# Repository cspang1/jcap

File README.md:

<h1 align="center"></h1>

<p align="center"><b>Check out the <a href="https://github.com/cspang1/JCAP/wiki">Project Wiki</a> for the development log</b></p> 
<p align="center"><b>A custom game resource creation software suite <a href="https://github.com/cspang1/jide">is being developed</a> for the inaugural JCAP release!</b></p> 

<hr>

<p>JCAP is a project with the goal of developing a <a href="https://www.mikesarcade.com/cgi-bin/spies.cgi?action=url&type=pinout&page=Jamma.html">JAMMA arcade standard</a> compatible game board using the <a href="https://www.parallax.com/product/p8x32a-q44">Parallax Propeller 1 (P8X32A) microcontroller</a> upon which a user can implement their own custom arcade game, either from scratch or by using the library of graphics, sound, input, and other drivers developed under the project. Ultimately, the project will provide all of the following in such a way that a user has everything they need to implement their own arcade game and have a PCB printed to build it on:</p>

<ul>
  <li>VGA video driver</li>
  <li>Sprite/tile based graphics driver</li>
  <li>PWM sound driver</li>
  <li>Serialized input driver</li>
  <li>Game engine</li>
  <li>Board schematic</li>
  <li>PCB .gerber files</li>
  <li>PCB BOM</li>
</ul>

<h1 align="center">Contribution Guidelines</h1>
<p>On the off chance anyone is interested in contributing to JCAP, there are some basic standards which should be ahered to:</p>

<ol>
  <li>Document everything! For code documentation, use existing code (e.g. Dev/Input/Software/input.spin) as an example. PASM should be documented somewhat anal-retentively, line-by-line, with block comments for routines and subroutines. Header comments should follow the same standard established by existing code as well.</li>
  <li>Any discovered problems/concerns/features that you won't be addressing with your current commit need to have an issue created and assigned to the appropriate person(s), tag, milestone, and project. This eliminates the risk of development amnesia. Additionally, when a commit has satisfied an issue, the commit hash should be referenced in the closing comment of the issue.</li>
  <li>Commit messages need to at a minimum broadly describe each change made to the repository. Whether it's fixing a bug, adding a feature, adding a new datasheet, or updating some indentation, one should be able to read the commit message and understand immediately what's been done to the repo.</li>
  <li>Any documents (manuals, datasheets, tutorials) which are critical to your contributions should be placed in their appropriate subdirectories in /Docs. For similarly important generic links, place them in "Useful Links.txt" in /Docs.</li>
</ol>

<p>Pull requests that don't follow these guidelines will be rejected until corrections have been made. While this all may seem like an over-processed waste of time, an auxiliary goal for JCAP is to create a project which maintains the highest possible standards to prevent headache down the road and belay confusion to anyone on the outside looking in.</p>

<h1 align="center">Current Contributors</h1>
<p>The following individuals have contributed to JCAP:</p>

<ul>
  <li>Connor Spangler (cspang1)</li>
  <li>Marko Lukat (konimaru)</li>
</ul>

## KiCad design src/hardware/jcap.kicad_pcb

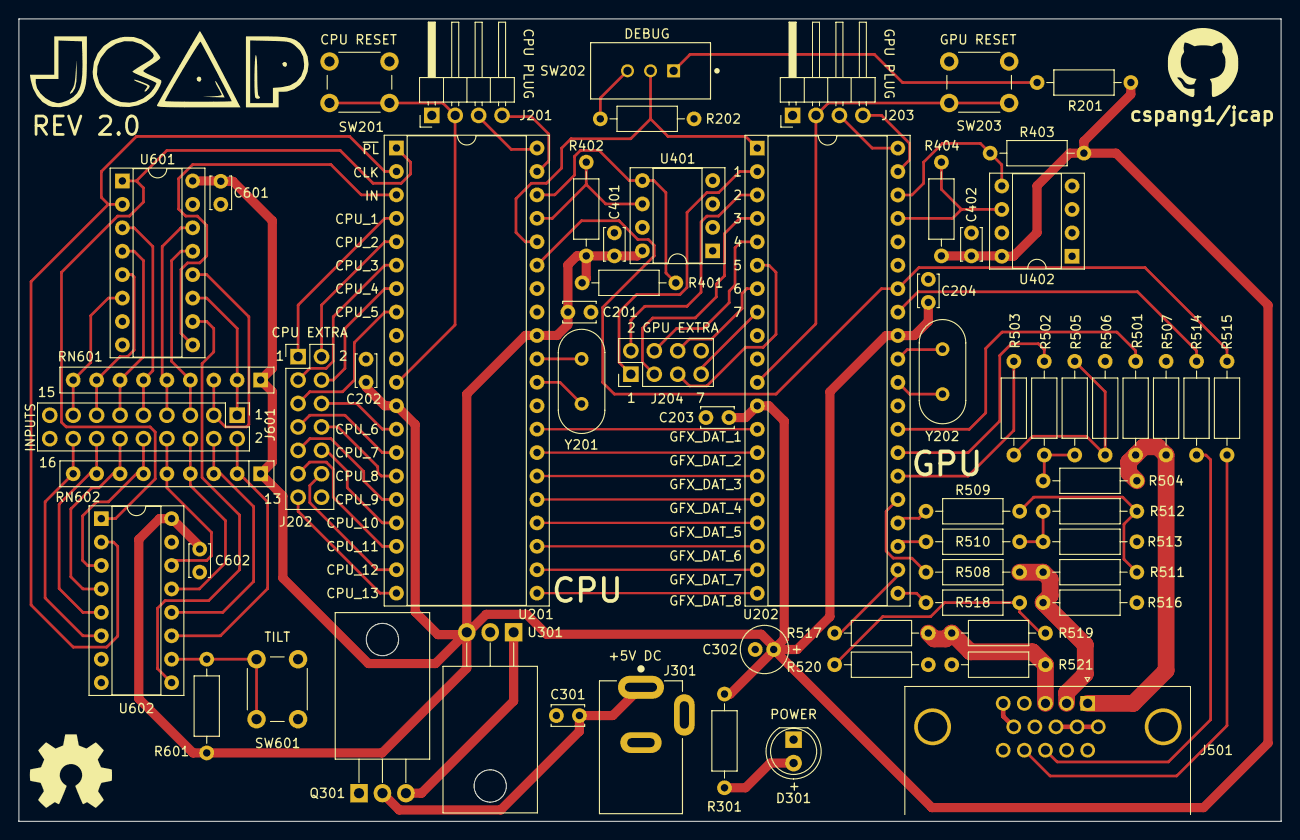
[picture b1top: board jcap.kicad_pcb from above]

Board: 2 copper layers, 136.8 x 87.0 mm, 63 parts (0 on the bottom side), 91 nets.

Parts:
C201, C202, C203, C204, C401, C402, C601, C602: 0.1u; C_Disc_D3.4mm_W2.1mm_P2.50mm
C301: .47u; C_Disc_D3.4mm_W2.1mm_P2.50mm
C302: 47u; C_Radial_D5.0mm_H11.0mm_P2.00mm
D301: POWER LED; LED_D5.0mm
J201: CPU PGMR; PinHeader_1x04_P2.54mm_Horizontal
J202: SPARE CPU HDR; PinHeader_2x07_P2.54mm_Vertical
J203: GPU PGMR; PinHeader_1x04_P2.54mm_Horizontal
J204: SPARE GPU HDR; PinHeader_2x04_P2.54mm_Vertical
J301: DC IN; CUI_PJ-202AH
J501: VGA OUT; 2311763-2
J601: CONTROLS; PinHeader_2x09_P2.54mm_Vertical
Q301: IPP80P03P4L-04; TO-220-3_Horizontal_TabDown
R201, R202, R601: 10K; R_Axial_DIN0207_L6.3mm_D2.5mm_P10.16mm_Horizontal
R301: 100; R_Axial_DIN0207_L6.3mm_D2.5mm_P10.16mm_Horizontal
R401, R402, R403, R404: 4.7K; R_Axial_DIN0207_L6.3mm_D2.5mm_P10.16mm_Horizontal
R501, R502, R503, R506, R508, R509, R510, R513: 309; R_Axial_DIN0207_L6.3mm_D2.5mm_P10.16mm_Horizontal
R504, R505, R511, R512: 154; R_Axial_DIN0207_L6.3mm_D2.5mm_P10.16mm_Horizontal
R507, R516: 147; R_Axial_DIN0207_L6.3mm_D2.5mm_P10.16mm_Horizontal
R514, R515: 220; R_Axial_DIN0207_L6.3mm_D2.5mm_P10.16mm_Horizontal
R517, R518, R520: 267; R_Axial_DIN0207_L6.3mm_D2.5mm_P10.16mm_Horizontal
R519: 133; R_Axial_DIN0207_L6.3mm_D2.5mm_P10.16mm_Horizontal
R521: 174; R_Axial_DIN0207_L6.3mm_D2.5mm_P10.16mm_Horizontal
RN601, RN602: 10K; R_Array_SIP9
SW201: CPU ~{RES}; SW_PUSH_6mm_H5mm
SW202: DEBUG; SW_1825159-1
SW203: GPU ~{RES}; SW_PUSH_6mm_H5mm
SW601: TILT; SW_PUSH_6mm_H5mm
U201, U202: P8X32A; DIP-40_W15.24mm_Socket
U301: LM3940IT; TO-220-3_Horizontal_TabDown
U401, U402: 24LC256; DIP-8_W7.62mm_Socket
U601, U602: 74HC165; DIP-16_W7.62mm_Socket
Y201, Y202: 6.5MHz; Crystal_HC49-U_Vertical

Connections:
+3.3V: C201.2, C202.2, C203.2, C204.2, C302.1, C401.2, C402.2, C601.2, C602.2, R201.2, R301.1, R401.2, R402.2, R403.2, R404.2, R601.2, RN601.1 (common), RN602.1 (common), U201.12 (VDD), U201.32 (VDD), U202.12 (VDD), U202.32 (VDD), U301.3 (OUT), U401.8 (VCC), U402.8 (VCC), U601.16 (VCC), U602.16 (VCC)
/Input/IN1: J601.1, RN601.2 (R1), U601.11 (D0)
/Input/IN2: J601.3, RN601.3 (R2), U601.12 (D1)
/Input/IN3: J601.5, RN601.4 (R3), U601.13 (D2)
/Input/IN4: J601.7, RN601.5 (R4), U601.14 (D3)
/Input/IN5: J601.9, RN601.6 (R5), U601.3 (D4)
/Input/IN6: J601.11, RN601.7 (R6), U601.4 (D5)
/Input/IN7: J601.13, RN601.8 (R7), U601.5 (D6)
/Input/IN8: J601.15, RN601.9 (R8), U601.6 (D7)
/Input/IN9: J601.2, RN602.2 (R1), U602.11 (D0)
/Input/IN10: J601.4, RN602.3 (R2), U602.12 (D1)
/Input/IN11: J601.6, RN602.4 (R3), U602.13 (D2)
/Input/IN12: J601.8, RN602.5 (R4), U602.14 (D3)
/Input/IN13: J601.10, RN602.6 (R5), U602.3 (D4)
/Input/IN14: J601.12, RN602.7 (R6), U602.4 (D5)
/Input/IN15: J601.14, RN602.8 (R7), U602.5 (D6)
/Input/IN16: J601.16, RN602.9 (R8), U602.6 (D7)
/Input/SHIFT_IN: U601.10 (DS), U602.9 (Q7)
/Propellers/CPU_SPARE_1: J202.1, U201.4 (P3)
/Propellers/CPU_SPARE_2: J202.2, U201.5 (P4)
/Propellers/CPU_SPARE_3: J202.3, U201.6 (P5)
/Propellers/CPU_SPARE_4: J202.4, U201.7 (P6)
/Propellers/CPU_SPARE_5: J202.5, U201.8 (P7)
/Propellers/CPU_SPARE_6: J202.6, U201.13 (P8)
/Propellers/CPU_SPARE_7: J202.7, U201.14 (P9)
/Propellers/CPU_SPARE_8: J202.8, U201.15 (P10)
/Propellers/CPU_SPARE_9: J202.9, U201.16 (P11)
/Propellers/CPU_SPARE_10: J202.10, U201.17 (P12)
/Propellers/CPU_SPARE_11: J202.11, U201.18 (P13)
/Propellers/CPU_SPARE_12: J202.12, U201.19 (P14)
/Propellers/CPU_SPARE_13: J202.13, U201.20 (P15)
/Propellers/DEBUG: SW202.2, U201.36 (P27), U202.1 (P0)
/Propellers/GFX_DAT_1: U201.28 (P23), U202.13 (P8)
/Propellers/GFX_DAT_2: U201.27 (P22), U202.14 (P9)
/Propellers/GFX_DAT_3: U201.26 (P21), U202.15 (P10)
/Propellers/GFX_DAT_4: U201.25 (P20), U202.16 (P11)
/Propellers/GFX_DAT_5: U201.24 (P19), U202.17 (P12)
/Propellers/GFX_DAT_6: U201.23 (P18), U202.18 (P13)
/Propellers/GFX_DAT_7: U201.22 (P17), U202.19 (P14)
/Propellers/GFX_DAT_8: U201.21 (P16), U202.20 (P15)
/Propellers/GPU_SPARE_1: J204.1, U202.2 (P1)
/Propellers/GPU_SPARE_2: J204.2, U202.3 (P2)
/Propellers/GPU_SPARE_3: J204.3, U202.4 (P3)
/Propellers/GPU_SPARE_4: J204.4, U202.5 (P4)
/Propellers/GPU_SPARE_5: J204.5, U202.6 (P5)
/Propellers/GPU_SPARE_6: J204.6, U202.7 (P6)
/Propellers/GPU_SPARE_7: J204.7, U202.8 (P7)
/Propellers/SER_RX_CPU: J201.4, U201.39 (P30)
/Propellers/SER_RX_GPU: J203.4, U202.39 (P30)
/Propellers/SER_TX_CPU: J201.3, U201.40 (P31)
/Propellers/SER_TX_GPU: J203.3, U202.40 (P31)
/Propellers/~SER_RES_CPU: J201.2, SW201.2, U201.11 (~RES)
/Propellers/~SER_RES_GPU: J203.2, SW203.2, U202.11 (~RES)
/VGA_DAC/BLUE_OUT: J501.3, R517.1, R519.1, R521.2
/VGA_DAC/GREEN_OUT: J501.2, R508.1, R511.1, R516.2
/VGA_DAC/RED_OUT: J501.1, R501.1, R504.1, R507.2
BLUE1: R517.2, U202.22 (P17)
BLUE2: R518.2, U202.21 (P16)
GND: C201.1, C202.1, C203.1, C204.1, C301.1, C302.2, C401.1, C402.1, C601.1, C602.1, D301.1 (K), J201.1, J202.14, J203.1, J204.8, J301.2, J301.3, J501.0, J501.5, J501.6, J501.7, J501.8, J501.10, J601.17, J601.18, Q301.1 (G), R202.2, R506.2, R507.1, R513.2, R516.1, R520.2, R521.1, SW201.1, SW203.1, SW601.1, U201.9 (VSS), U201.10 (~BOE), U201.29 (VSS), U202.9 (VSS), U202.10 (~BOE), U202.29 (VSS), U301.2 (GND), U401.1 (A0), U401.2 (A1), U401.3 (A2), U401.4 (GND), U401.7 (WP), U402.1 (A0), U402.2 (A1), U402.3 (A2), U402.4 (GND), U402.7 (WP), U601.8 (GND), U601.15 (~CE), U602.8 (GND), U602.15 (~CE)
GREEN1: R508.2, U202.25 (P20)
GREEN2: R509.2, U202.24 (P19)
GREEN3: R510.2, U202.23 (P18)
H_SYNC: R514.1, U202.33 (P24)
INPUTS: U201.3 (P2), U601.9 (Q7)
INPUTS_CLK: U201.2 (P1), U601.2 (CP), U602.2 (CP)
unnamed: D301.2 (A), R301.2
unnamed: J501.13, R514.2
unnamed: J501.14, R515.2
unnamed: C301.2, J301.1, Q301.2 (D)
unnamed: Q301.3 (S), U301.1 (IN)
unnamed: R201.1, SW202.1
unnamed: R202.1, SW202.3
unnamed: R502.1, R504.2, R505.1
unnamed: R503.1, R505.2, R506.1
unnamed: R509.1, R511.2, R512.1
unnamed: R510.1, R512.2, R513.1
unnamed: R518.1, R519.2, R520.1
unnamed: U201.30 (XI), Y201.2
unnamed: U201.31 (XO), Y201.1
unnamed: U202.30 (XI), Y202.2
unnamed: U202.31 (XO), Y202.1
unnamed: R601.1, SW601.2, U602.10 (DS)
RED1: R501.2, U202.28 (P23)
RED2: R502.2, U202.27 (P22)
RED3: R503.2, U202.26 (P21)
SCL_CPU: R402.1, U201.37 (P28), U401.6 (SCL)
SCL_GPU: R404.1, U202.37 (P28), U402.6 (SCL)
SDA_CPU: R401.1, U201.38 (P29), U401.5 (SDA)
SDA_GPU: R403.1, U202.38 (P29), U402.5 (SDA)
V_SYNC: R515.1, U201.35 (P26), U202.34 (P25)
~INPUTS_PL: U201.1 (P0), U601.1 (~PL), U602.1 (~PL)

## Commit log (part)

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2017-06-06 Minor cosmetic change to input.spin
2017-06-06 Refactored input.spin layout
2017-06-06 Fixed README.md formatting
2017-06-07 Added links concerning 240p video to Useful Links.txt
2017-06-10 Created wip/video/vga branch for developing VGA video. Added a couple DAC examples. Created vga.spin file.
2017-06-14 Updated counter PLL calculator
2017-06-15 Began adding video generation logic to vga.spin. Populated counter PLL calculator w/ 640x480 @ 60 Hz values.
2017-10-26 Started adding test code/values to develop a monochromatic 640x480 60Hz VGA routine
2017-10-27 Modified vga.spin to implement vertical sync area; full vga monochromatic measuring via oscilloscope ready
2017-10-27 Updated, moved, and renamed P8X32A/DE0-Nano pinout image
2017-10-27 Modified vga.spin so test colors step up gradually for testing. Added R-2R_DAC.asc LTSpice circuit model to test and verify VGA DAC functionality.
2017-10-27 .gitignore is now working
2017-10-28 Updated vga.spin commenting
2017-10-30 Updated vga.spin VGA driver to render @ 16x16 pixel tile demensions of 10x12 tiles to support tile graphics also added for next iteration of testing
2017-10-30 Began implementing tile-based graphics
2017-10-30 Updated vga.spin to correctly reference tile pointers (par passed to cog only contains address of address of tile/color resources, so needed extra rdlong)
2017-10-31 Updated vga.spin commenting. Added another tile map for testing. Removed fit directive.
2017-11-01 Objectified vga driver
2017-11-02 Refactored vga driver to be parameterized
2017-11-03 Added 8x8 compatible tile map to vga_test.spin, and reorganized tile palette to take into account video generator mirroring
2017-11-03 Update VGA driver comments
2017-11-04 Added link to wiki to readme
2017-11-04 Updated game logic to use inputs to manipulate and store x/y game position within game map boundary
2017-11-05 Prepared game.spin to perform scrolling via VGA driver
2017-11-05 Started refactoring game system to use rising edge input logic; running into apparent debouncing issue
2017-11-06 Updated vga.spin to change VGA outputs to highest 8 GPIO pins (freeing up LED outputs for testing). Updated game logic to update position registers via buttons as well as explicitly manipulate the ti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
2017-11-07 Updated compatible tile dimension calculator
2017-11-07 Refactored VGA driver to iteratively load hub variables into cog registers
2017-11-10 Prepared wip branches for multi-cog video dev
2017-11-10 Established multi-cog start/stop routines for graphics driver
2017-11-11 Added graphics stop routine and refactored
2017-11-13 Fixed misidentified bug w/ VGA driver start/stop via inputs
2017-11-14 Added VGA driver cog synchronization, and overhauled some commenting and implementation details
2017-11-15 Refactor in preparation for multicog overhaul
2017-11-16 Began multicog VGA refactor; currently experiencing bizarre behavior w/ only > 2 cogs working.
2017-11-17 Continued refactor of graphics/VGA system
2017-11-19 Began integrating tile map system with multicog VGA driver
2017-11-20 Minor multicog refactor modifications
2017-11-21 Removed unecessary variable reservations
2017-11-22 Corrected errant buffer reading/writing
2017-11-22 Minor multicog VGA driver logic refactor
2017-11-22 Refactored VGA tile and color retrieval
2017-11-23 Heavily refactored VGA/graphics system to reduce memory footprint
2018-01-24 Removed vga + graphics objects; completely stripped game object and created reduced VGA display object
2018-01-24 Began implementing displaying with test values
2018-01-27 Changed default color
2018-01-27 Finalized display routine; locked-in 104 MHz clock freq
2018-01-28 Started render routine development
2018-01-28 Added multi-cog rendering and stop routines
2018-01-28 Added stop function to display routine and updates
2018-01-28 Updated cog scanline buffer writing routine
2018-01-29 Fixed missing last display line; implemented locks to set/get initial scanline indexes
2018-01-29 Prepared render routine for graphics generation implementation
2018-01-29 Added graphics resources and base address pointers to render
2018-01-30 Refactored graphics resource initialization in render routine
2018-01-30 Fixed render semaphore bug; refactored hub RAM memory access
2018-01-31 Implemented map tile, tile palette, and color palette loading into render routine
2018-01-31 Fixed semaphore addressing in render routine
2018-02-02 Updated test tile map to border only
2018-02-02 Removed redundant rendering instructions
2018-02-03 Updated render system to support 16-color tiles
2018-02-03 Removed sound system placeholder
2018-02-04 Prepared graphics and render systems for sprite implementation
2018-02-04 Optimized vertical sprite rendering visibility check
2018-02-13 Started fleshing out horizontal bounds check; but will probably refactor both bounds checks to follow simple formula
2018-02-15 Finalized horizontal sprite visibility check
2018-02-15 Started implementing sprite pixel palette parsing
2018-02-15 Added sprite palette offset calculation (needs verification)
2018-02-16 Fixed scanline buffer out of bounds bug
2018-02-17 Fixed imput system off-by-one bug; began implementing spin interpreter sprite test routine
2018-02-17 Cosmetic changes
2018-02-18 Refactored srpite test routine; began implemented sprite mirroring
2018-02-19 Finalized sprite mirroring; improved sprite graphics test routine
2018-02-19 Added visible area immediate sprite wrapping to test routine
2018-02-19 Improved render cog system
2018-02-24 Removed sprite sizing from render routine
2018-03-02 Fixed off-by-one input polling issue; optimized graphics test routine
2018-03-02 Minor test system improvement
2018-04-27 Fixed some HTML
2018-05-01 Cosmetic variable name change
2018-05-01 Reverted render routine to pre-scrolling
2018-05-01 Update issue templates
2018-05-02 Minor fix
2018-05-02 Started refactoring graphics resources memory model
2018-05-08 OSX PropIDE tab check
2018-05-08 Added TX variable pulling and control flag waiting
2018-05-09 Explicitly defined TX routine FRQA; cosmetic changes
2018-05-10 Created TX/RX testbench; reverted graphics testbench
2018-05-10 Implemented RX routine framework
2018-05-16 Updated scratchpad
2018-05-18 Overhauled TX/RX routines to fix timing/pin errors
2018-05-25 Incorporated graphics routines into RX; ready to implement watchdog
2018-05-26 Cosmetic change
2018-05-26 Began hardcoding/flattening memory model
2018-05-27 Successfully implemented dual-prop CPU/GPU system
2018-05-27 Integrated input test routine into CPU/GPU system
2018-06-06 Fixed sprite tearing bug by waiting for next data buffer
2018-06-07 Successfully implemented 6 render cog system
2018-06-08 Simplified TX memory model
2018-06-08 Precalculated TX gfx buff size
2018-06-08 Minor TX routine refactor
2018-06-08 Added calculation of graphics resources buffer size to RX routine
2018-06-08 File rename and refactor
2018-06-11 Began defining hsync parameters
2018-06-12 Implemented VSync; blowing final Hor BP time
2018-06-12 Implemented double scanline sync issue fix; ready for validation
2018-06-13 Revert "Experimental logic flow"
    This reverts commit f045fb5e9e0690fd27d89669bea25c4eb440f6c9.
2018-06-13 Another experimental logic refactor
2018-06-14 Implemented 8-bit driver; complete display driver refactor
2018-06-14 Implemented sprite index 0 transparency; need verification
2018-06-15 Finalized 8-bit sprite transparency
2018-06-15 Successfully implemented mem-based data signal
2018-06-15 Updated datasheets
2018-06-21 Added fast TX/RX routines; updated .gitignore w/ *.binary
2018-06-26 Fixed TX refactor bug
2018-06-26 Further refactored RX routine; synced TX w/ VSync
2018-06-27 Tab refactor
2019-03-22 Implemented potential startup de-sync fix; need to verify
2019-05-15 Fixed GFX de-sync issue
2019-05-16 Implemented system setting header file; refactored sync handshake constants
2019-05-17 Implemented up to step 3 of smooth horizontal scrolling
2019-05-17 Implemented horizontal scroll wrapping
2019-05-17 Finalized horizontal scroll wrapping
2019-05-18 Decreased cycle count in tile load routine
2019-05-18 Simplified horizontal mirror logic
2019-05-20 Greatly reduced instruction count in sprite render routine - only one more instr to remove
2019-05-21 Added several optimizations - needs verification
2019-05-21 Implemented pre-determined tld routine call - needs verification
2019-05-22 Working out bugs in new tile render code
2019-05-22 Almost there...
2019-05-22 Removed debug line
2019-05-22 Completely cleaned up render routine - ready for final tld phsb opt
2019-05-22 Finalized significant rendering optimizations
2019-05-22 Even more trivial cosmetic change
2019-05-22 Additional render optimizations
2019-05-22 Additional cosmetic and cycle reduction improvements
2019-05-22 Implemented Marko Lukat's nifty tile load optimization
2019-05-22 Fixed tile loading logic error
2019-05-22 Cleaned up render code formatting
2019-05-23 Minor render logic updates
2019-05-23 Minor variable change
2019-05-24 Revert "Implemented Marko Lukat's fast transfer routine"
    This reverts commit 291705fcefd086d3dbf9a9499fddb96928b4269d.
2019-05-25 Revert "Unrolled slbuff write loop once - can be done more"
    This reverts commit 7ddb7547ae66e4ffe5f8f36ff0ef46ea52901674.
2019-05-25 Implemented faster scanline display routine - need to debug
2019-05-25 Cleaned up final display driver code
2019-05-26 Functional vertical scrolling!
2019-05-26 Cleaned up render code
2019-10-25 Successfully implemented extended buffer horizontal wrapping
2019-10-25 Refactored system variables and tidied up
2019-10-25 Added test sprite resources; refactored CPU-side sprite logic in prep for wide sprites
2019-10-27 Successfully implemented wide and mirrored sprites!
2019-10-27 Removed unecessary CPU lines
2019-10-28 Began implementing vertical sprite changes
2019-10-28 Finalized sprite sizing work
2019-10-29 Overhauled screen position system to prepare for parallax implementation
2019-10-29 Successfully implemented initial parallax config
2019-10-31 Successfully implemented multi-line parallax scrolling!
2019-11-01 Implemented full-featured parallax scrolling, however...
    The original parallax implementation (bc3e7459c6c584dea46de2375874c4eb9eae083e) is limited by the intentionally programmed assumption that the next scanline on a cog would have only one line between 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
2019-11-08 Updated code for compatability with new hardware layout
2019-11-09 Major input system update along with color test setup
2019-11-11 Prep'd demo resources and data structures
2019-11-12 Addt'l updates to graphics demo resources
2019-11-12 Implemented initial sinusoidal parallaxing demo
2019-11-12 Testing parallaxing functions
2019-11-13 Finalized waterfall gfx
2019-11-13 Addt'l gfx updates
2019-11-14 Refined parallax region move code
2019-11-14 Refactored demo logic into libs
2019-11-15 Implemented gfx_utils getters and sprite animation
2019-11-15 Implemented cmd line compile+load script via bstc
2019-11-15 Fancier animations
2019-11-16 Moved all graphics resources to external files & updated load script(s)
2019-11-17 Implemented new sprite
2019-11-17 Fixed bug in and updated sysload
2019-11-17 Removed Hardware dir
2019-11-19 Minor update
2019-11-21 Minor updates
2020-01-18 Implemented +16 tall sprites
2020-04-02 Added JIDE to README
2020-06-08 Updated vga_display FRQA to stabalize PLL
2020-06-12 Implemented uC ID system
2023-08-31 Additional documentation overhaul
2023-09-05 Started KiCad project
2023-09-06 Continued developing JCAP schematic
2023-09-07 Started developing PCB layout
2023-09-07 Updated netclasses and PCB specs
2023-09-07 Fixed netclasses
2023-09-08 Fixed lib footprint 3D model refs
2023-09-08 Updated input header pinout
2023-09-16 Added silkscreen - review ready
2023-09-17 Finalized review schematic & pcb
2023-09-18 75 ohm DAC traces final refactor
2023-09-19 Implemented review changes - missing reverse polarity protection
2023-09-24 Finalized dev PCB for 1st run
2023-09-26 Finalized dev board administrivia
2023-10-02 Updated firmware for new pinout
2023-10-03 Fixed sync pin mixup - Rev 2.0
2023-10-03 Sysload update f/ bstc
2023-10-03 Added second gnd to input hdr
2023-10-07 Swapped H/VSync pins
